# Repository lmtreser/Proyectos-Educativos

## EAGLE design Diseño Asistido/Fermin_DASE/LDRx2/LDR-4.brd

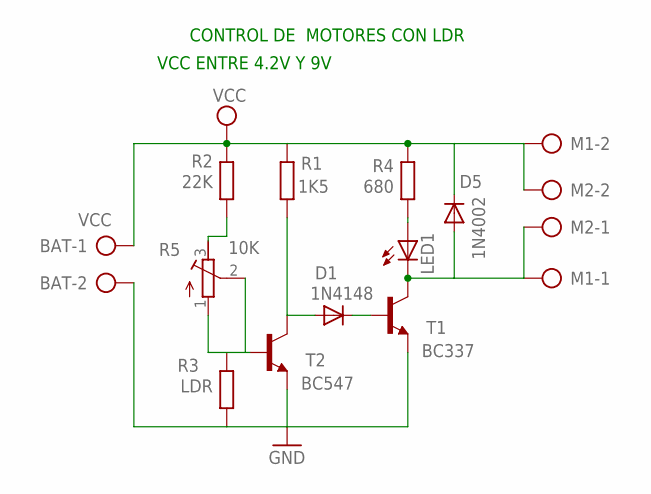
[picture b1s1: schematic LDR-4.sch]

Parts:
BAT: VCC; AK500/2
D1: 1N4148; DO35-7
D5: 1N4002; DO41-10
LED1: LED3MM
M1, M2: AK500/2
R1: 1K5; 0207/7
R2: 22K; 0207/7
R3: LDR; 0204/5
R4: 680; 0207/7
R5: 10K; RTRIM64W
T1: BC337; TO92-CBE
T2: BC547; TO92-CBE

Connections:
GND: BAT.2, R3.1, T1.E, T2.E
unnamed: D1.C, T1.B
unnamed: D1.A, R1.1, T2.C
unnamed: D5.A, LED1.K (C), M1.1, M2.1, T1.C
unnamed: R2.1, R5.3 (E)
unnamed: LED1.A, R4.1
unnamed: R3.2, R5.1 (A), R5.2 (S), T2.B
VCC: BAT.1, D5.C, M1.2, M2.2, R1.2, R2.2, R4.2

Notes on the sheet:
CONTROL DE MOTORES CON LDR
VCC ENTRE 4.2V Y 9V

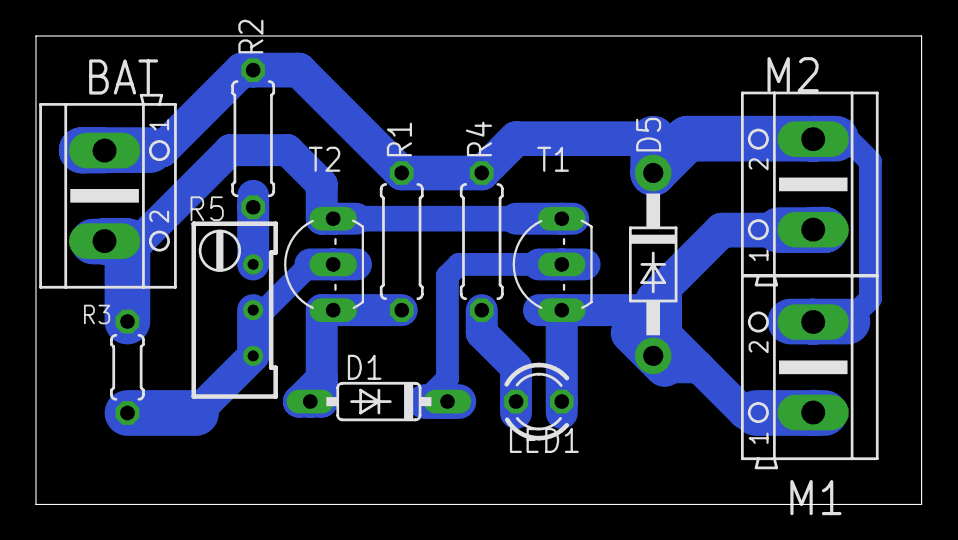
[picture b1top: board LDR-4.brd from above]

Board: 2 copper layers, 49.2 x 26.0 mm, 13 parts (0 on the bottom side), 8 nets.

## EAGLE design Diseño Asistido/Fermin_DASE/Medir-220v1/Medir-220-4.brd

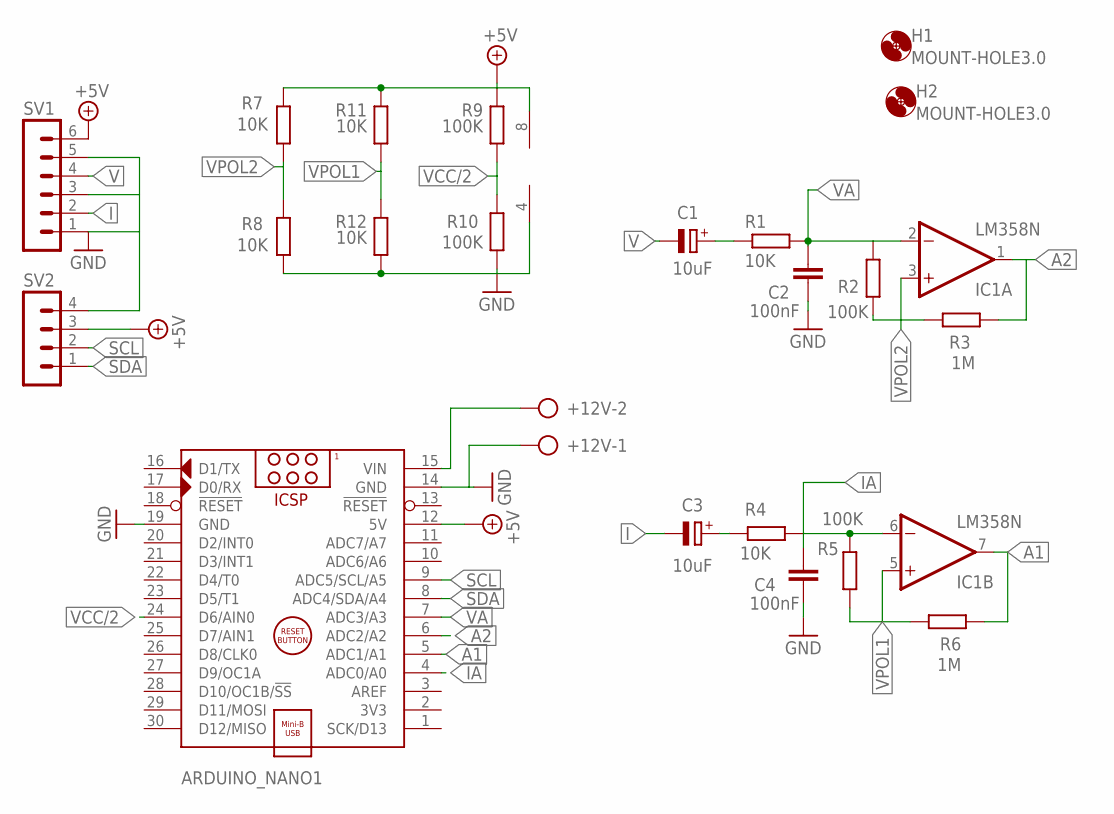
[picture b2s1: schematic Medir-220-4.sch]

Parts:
+12V: AK500/2
ARDUINO_NANO1: ARDUINO_NANO
C1, C3: 10uF; E2,5-5
C2, C4: 100nF; C050-025X075
H1, H2: MOUNT-HOLE3.0; 3,0
IC1: LM358N; DIL08
R1, R4, R7, R8, R11, R12: 10K; 0207/7
R2, R5: 100K; 0207/7
R3, R6: 1M; 0207/7
R9, R10: 100K; 0207/10
SV1: MA06-1
SV2: MA04-1

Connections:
+5V: ARDUINO_NANO1.12 (5V), IC1.8 (V+), R7.1, R9.2, R11.2, SV1.6, SV2.3
A1: ARDUINO_NANO1.5 (ADC1/A1), IC1.7 (OUT), R6.1
A2: ARDUINO_NANO1.6 (ADC2/A2), IC1.1 (OUT), R3.1
GND: +12V.1, ARDUINO_NANO1.14 (GND), ARDUINO_NANO1.19 (GND), C2.2, C4.2, IC1.4 (V-), R8.2, R10.1, R12.1, SV1.1, SV1.3, SV1.5, SV2.4
I: C3.-, SV1.2
IA: ARDUINO_NANO1.4 (ADC0/A0), C4.1, IC1.6 (-IN), R4.1, R5.1
unnamed: C3.+, R4.2
unnamed: C1.+, R1.2
unnamed: +12V.2, ARDUINO_NANO1.15 (VIN)
SCL: ARDUINO_NANO1.9 (ADC5/SCL/A5), SV2.2
SDA: ARDUINO_NANO1.8 (ADC4/SDA/A4), SV2.1
V: C1.-, SV1.4
VA: ARDUINO_NANO1.7 (ADC3/A3), C2.1, IC1.2 (-IN), R1.1, R2.2
VCC/2: ARDUINO_NANO1.24 (D6/AIN0), R9.1, R10.2
VPOL1: IC1.5 (+IN), R5.2, R6.2, R11.1, R12.2
VPOL2: IC1.3 (+IN), R2.1, R3.2, R7.2, R8.1

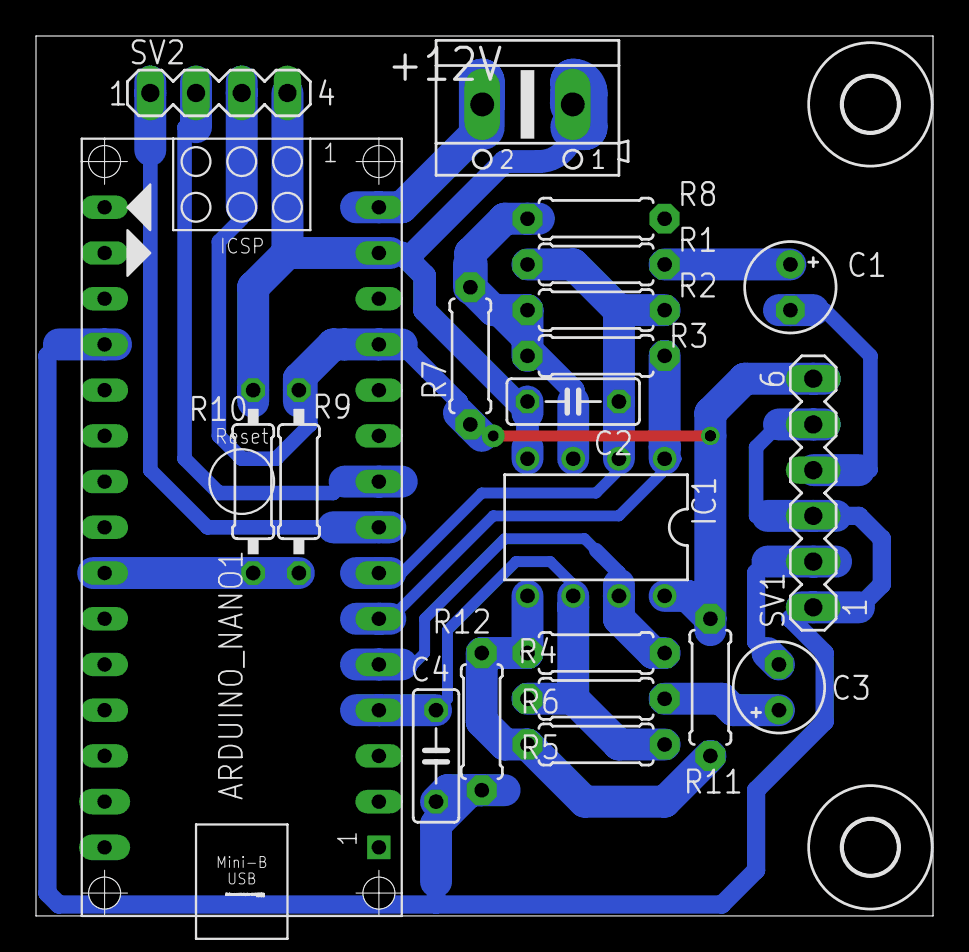
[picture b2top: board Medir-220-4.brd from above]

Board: 2 copper layers, 49.8 x 48.9 mm, 23 parts (0 on the bottom side), 16 nets.

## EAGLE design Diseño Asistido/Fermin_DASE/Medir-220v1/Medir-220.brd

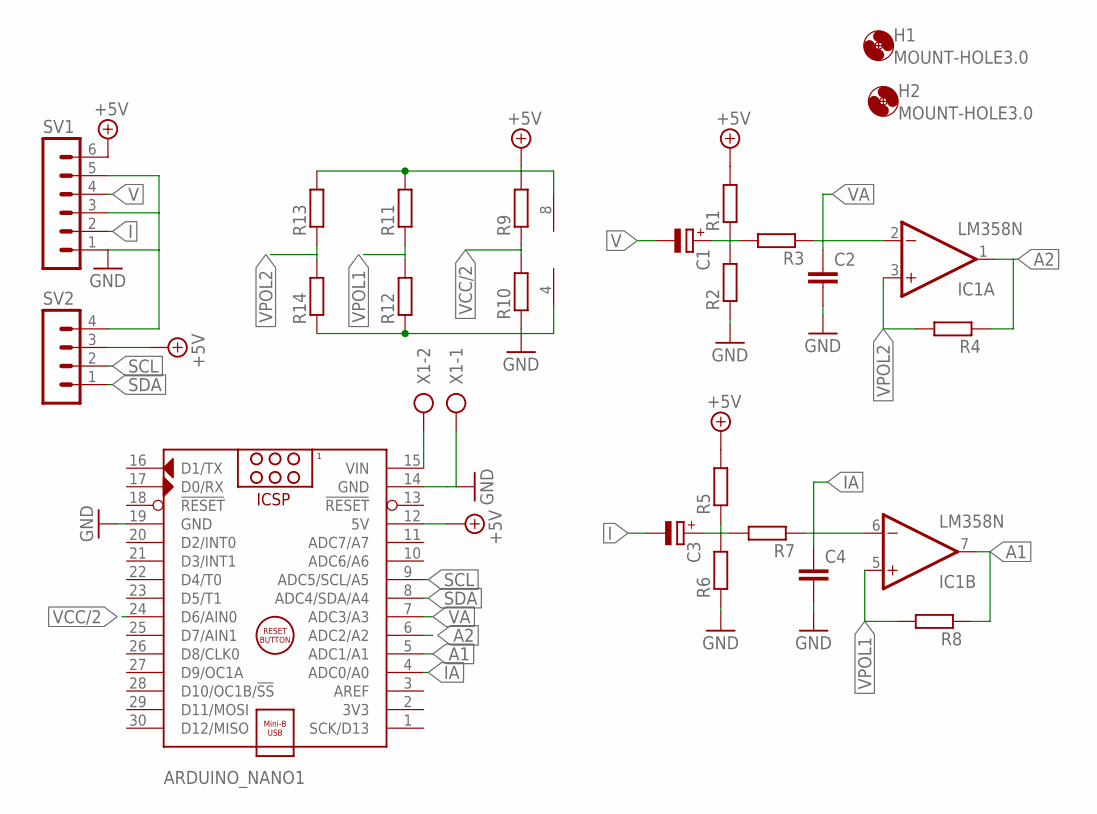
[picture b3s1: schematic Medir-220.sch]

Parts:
ARDUINO_NANO1: ARDUINO_NANO
C1, C3: CPOL-EUE2.5-5; E2,5-5
C2, C4: C-EU050-025X075; C050-025X075
H1, H2: MOUNT-HOLE3.0; 3,0
IC1: LM358N; DIL08
R1, R2, R3, R4, R5, R6, R7, R8, R11, R12, R13, R14: R-EU_0207/7; 0207/7
R9, R10: R-EU_0207/10; 0207/10
SV1: MA06-1
SV2: MA04-1
X1: AK500/2

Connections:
+5V: ARDUINO_NANO1.12 (5V), IC1.8 (V+), R1.2, R5.2, R9.2, R11.2, R13.2, SV1.6, SV2.3
A1: ARDUINO_NANO1.5 (ADC1/A1), IC1.7 (OUT), R8.1
A2: ARDUINO_NANO1.6 (ADC2/A2), IC1.1 (OUT), R4.1
GND: ARDUINO_NANO1.14 (GND), ARDUINO_NANO1.19 (GND), C2.2, C4.2, IC1.4 (V-), R2.1, R6.1, R10.1, R12.1, R14.1, SV1.1, SV1.3, SV1.5, SV2.4, X1.1
I: C3.-, SV1.2
IA: ARDUINO_NANO1.4 (ADC0/A0), C4.1, IC1.6 (-IN), R7.1
unnamed: C1.+, R1.1, R2.2, R3.2
unnamed: C3.+, R5.1, R6.2, R7.2
unnamed: ARDUINO_NANO1.15 (VIN), X1.2
SCL: ARDUINO_NANO1.9 (ADC5/SCL/A5), SV2.2
SDA: ARDUINO_NANO1.8 (ADC4/SDA/A4), SV2.1
V: C1.-, SV1.4
VA: ARDUINO_NANO1.7 (ADC3/A3), C2.1, IC1.2 (-IN), R3.1
VCC/2: ARDUINO_NANO1.24 (D6/AIN0), R9.1, R10.2
VPOL1: IC1.5 (+IN), R8.2, R11.1, R12.2
VPOL2: IC1.3 (+IN), R4.2, R13.1, R14.2

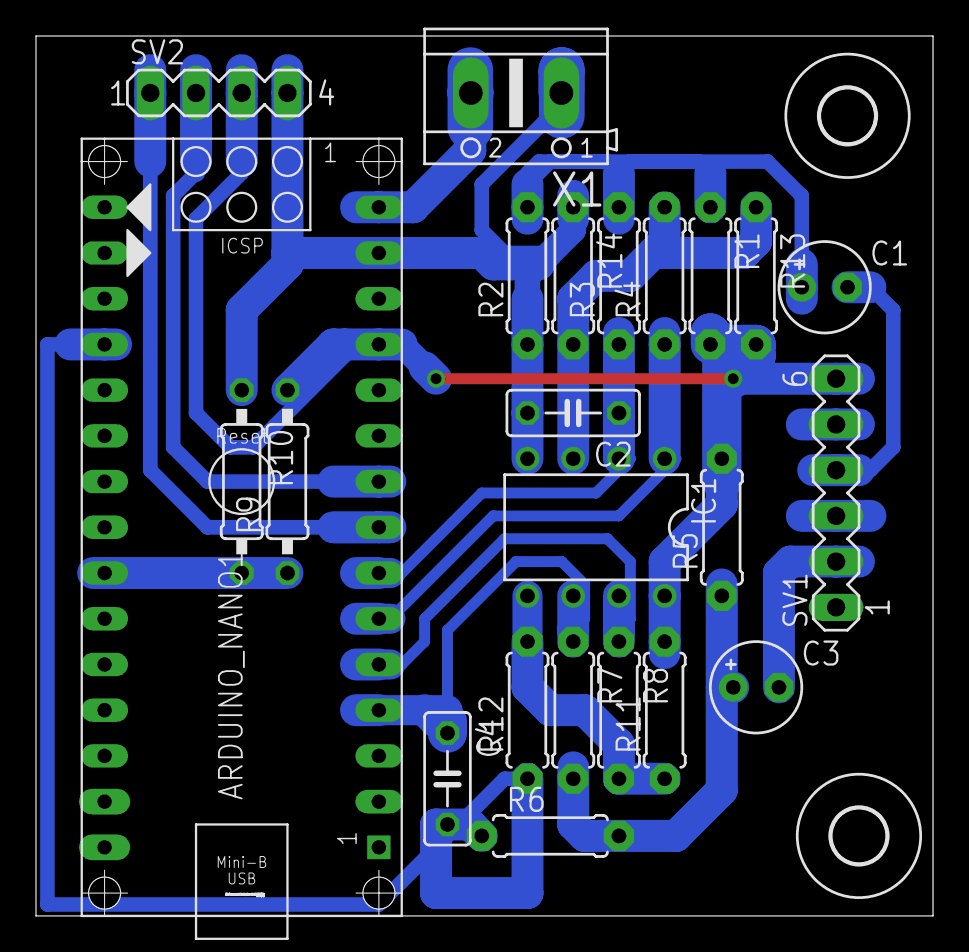
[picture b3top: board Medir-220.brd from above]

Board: 2 copper layers, 49.8 x 48.9 mm, 25 parts (0 on the bottom side), 16 nets.

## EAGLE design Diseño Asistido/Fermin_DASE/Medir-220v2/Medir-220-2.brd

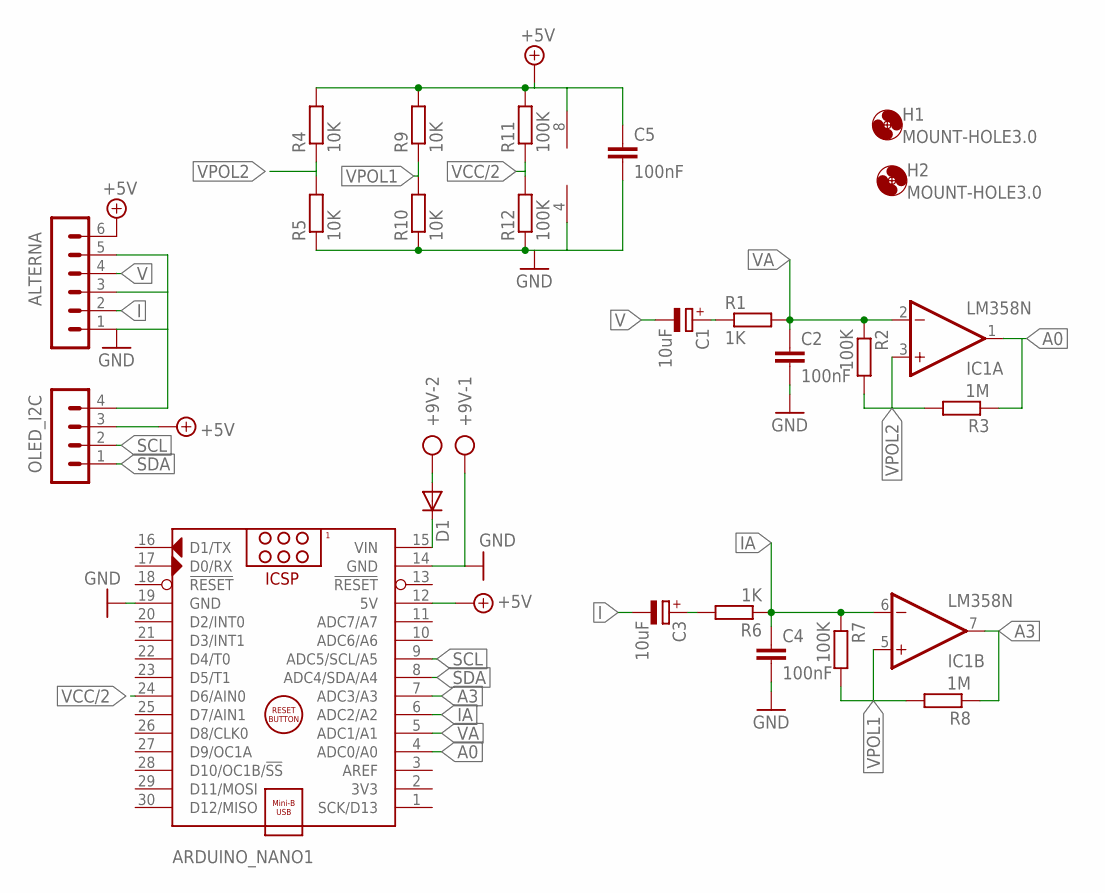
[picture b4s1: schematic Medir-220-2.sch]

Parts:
+9V: AK500/2
ALTERNA: MA06-1
ARDUINO_NANO1: ARDUINO_NANO
C1, C3: 10uF; E2,5-5
C2, C4: 100nF; C050-025X075
C5: 100nF; C025-025X050
D1: DIODE-D-2.5; D-2.5
H1, H2: MOUNT-HOLE3.0; 3,0
IC1: LM358N; DIL08
OLED_I2C: MA04-1
R1, R6: 1K; 0207/7
R2, R7: 100K; 0207/7
R3, R8: 1M; 0207/7
R4: 10K; 0207/10
R5, R9, R10: 10K; 0207/7
R11, R12: 100K; 0207/10

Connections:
+5V: ALTERNA.6, ARDUINO_NANO1.12 (5V), C5.1, IC1.8 (V+), OLED_I2C.3, R4.2, R9.2, R11.2
A0: ARDUINO_NANO1.4 (ADC0/A0), IC1.1 (OUT), R3.1
A3: ARDUINO_NANO1.7 (ADC3/A3), IC1.7 (OUT), R8.1
GND: +9V.1, ALTERNA.1, ALTERNA.3, ALTERNA.5, ARDUINO_NANO1.14 (GND), ARDUINO_NANO1.19 (GND), C2.2, C4.2, C5.2, IC1.4 (V-), OLED_I2C.4, R5.1, R10.1, R12.1
I: ALTERNA.2, C3.-
IA: ARDUINO_NANO1.6 (ADC2/A2), C4.1, IC1.6 (-IN), R6.1, R7.1
unnamed: C1.+, R1.1
unnamed: C3.+, R6.2
unnamed: +9V.2, D1.A
unnamed: ARDUINO_NANO1.15 (VIN), D1.C
SCL: ARDUINO_NANO1.9 (ADC5/SCL/A5), OLED_I2C.2
SDA: ARDUINO_NANO1.8 (ADC4/SDA/A4), OLED_I2C.1
V: ALTERNA.4, C1.-
VA: ARDUINO_NANO1.5 (ADC1/A1), C2.1, IC1.2 (-IN), R1.2, R2.1
VCC/2: ARDUINO_NANO1.24 (D6/AIN0), R11.1, R12.2
VPOL1: IC1.5 (+IN), R7.2, R8.2, R9.1, R10.2
VPOL2: IC1.3 (+IN), R2.2, R3.2, R4.1, R5.2

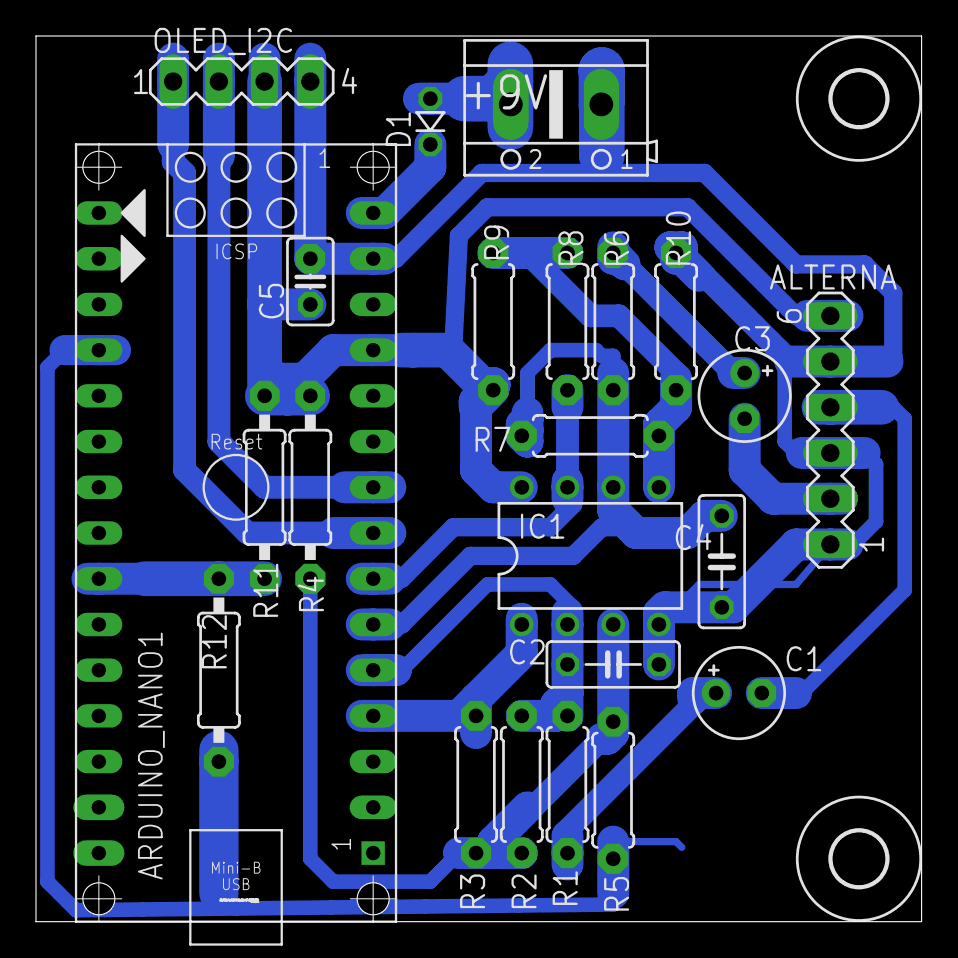
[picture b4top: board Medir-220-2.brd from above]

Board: 2 copper layers, 49.2 x 49.2 mm, 25 parts (0 on the bottom side), 17 nets.

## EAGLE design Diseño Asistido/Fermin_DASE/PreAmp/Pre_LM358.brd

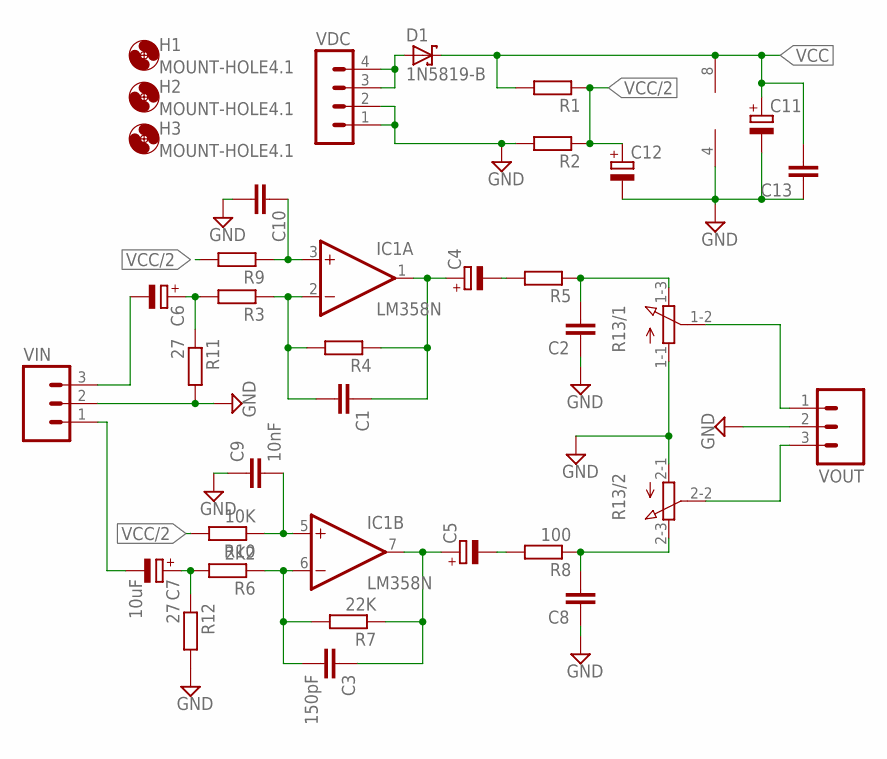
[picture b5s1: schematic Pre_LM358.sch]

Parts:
C1, C2, C8, C10, C13: C-EU025-025X050; C025-025X050
C3: 150pF; C025-025X050
C4, C5, C6: CPOL-EUE2.5-5; E2,5-5
C7: 10uF; E2,5-5
C9: 10nF; C025-025X050
C11: CPOL-EUE2.5-7; E2,5-7
C12: CPOL-EUE2-4; E2-4
D1: 1N5819-B; DO41-7.6
H1, H2, H3: MOUNT-HOLE4.1; 4,1
IC1: LM358N; DIL08
R1, R2, R3, R4, R5, R9: R-EU_0207/7; 0207/7
R6: 2K2; 0207/7
R7: 22K; 0207/7
R8: 100; 0207/7
R10: 10K; 0207/7
R11, R12: 27; 0207/7
R13: 3RP/1610G
VDC: MA04-1
VIN: MA03; 03P
VOUT: MA03; 03P

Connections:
GND: C2.1, C8.1, C9.1, C10.2, C11.-, C12.-, C13.1, IC1.4 (V-), R2.2, R11.2, R12.2, R13.1-1 (A), R13.2-1 (A), VDC.1, VDC.2, VIN.2, VOUT.2
unnamed: C6.+, R3.2, R11.1
unnamed: C7.+, R6.2, R12.1
unnamed: C1.2, IC1.2 (-IN), R3.1, R4.2
unnamed: C1.1, C4.+, IC1.1 (OUT), R4.1
unnamed: C4.-, R5.2
unnamed: C2.2, R5.1, R13.1-3 (E)
unnamed: C3.1, C5.+, IC1.7 (OUT), R7.1
unnamed: C5.-, R8.2
unnamed: C8.2, R8.1, R13.2-3 (E)
unnamed: C3.2, IC1.6 (-IN), R6.1, R7.2
unnamed: C7.-, VIN.1
unnamed: C6.-, VIN.3
unnamed: D1.A, VDC.3, VDC.4
unnamed: R13.2-2 (S), VOUT.3
unnamed: R13.1-2 (S), VOUT.1
unnamed: C10.1, IC1.3 (+IN), R9.1
unnamed: C9.2, IC1.5 (+IN), R10.1
VCC: C11.+, C13.2, D1.C, IC1.8 (V+), R1.2
VCC/2: C12.+, R1.1, R2.1, R9.2, R10.2

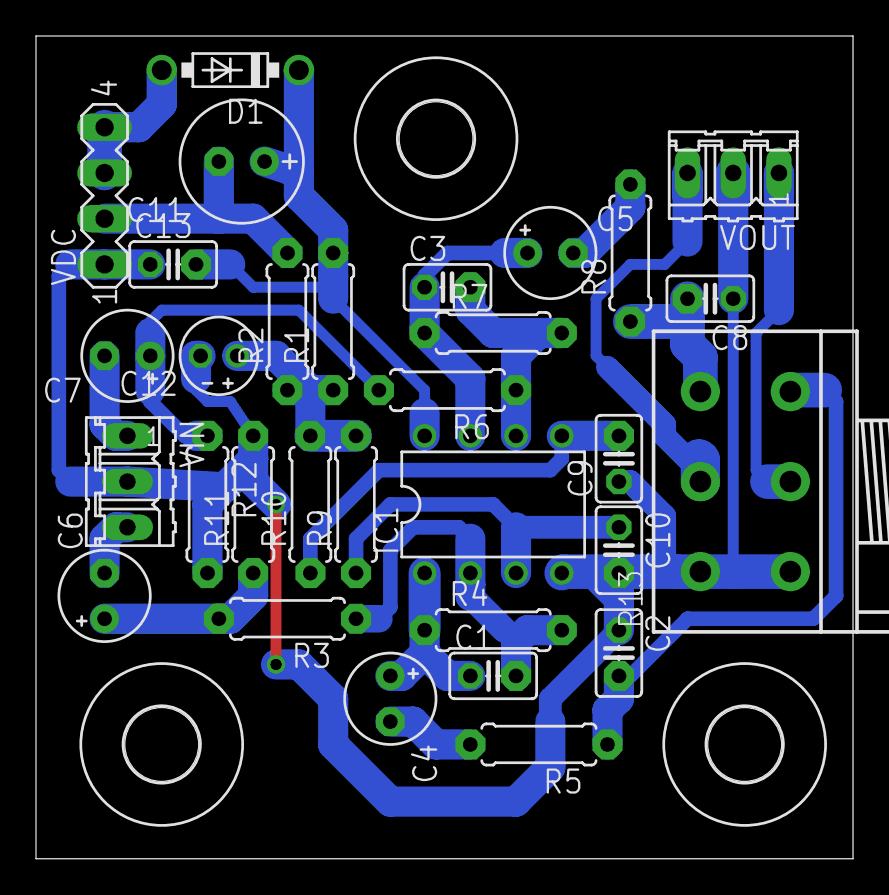
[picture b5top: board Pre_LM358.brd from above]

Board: 2 copper layers, 45.4 x 45.7 mm, 34 parts (0 on the bottom side), 20 nets.

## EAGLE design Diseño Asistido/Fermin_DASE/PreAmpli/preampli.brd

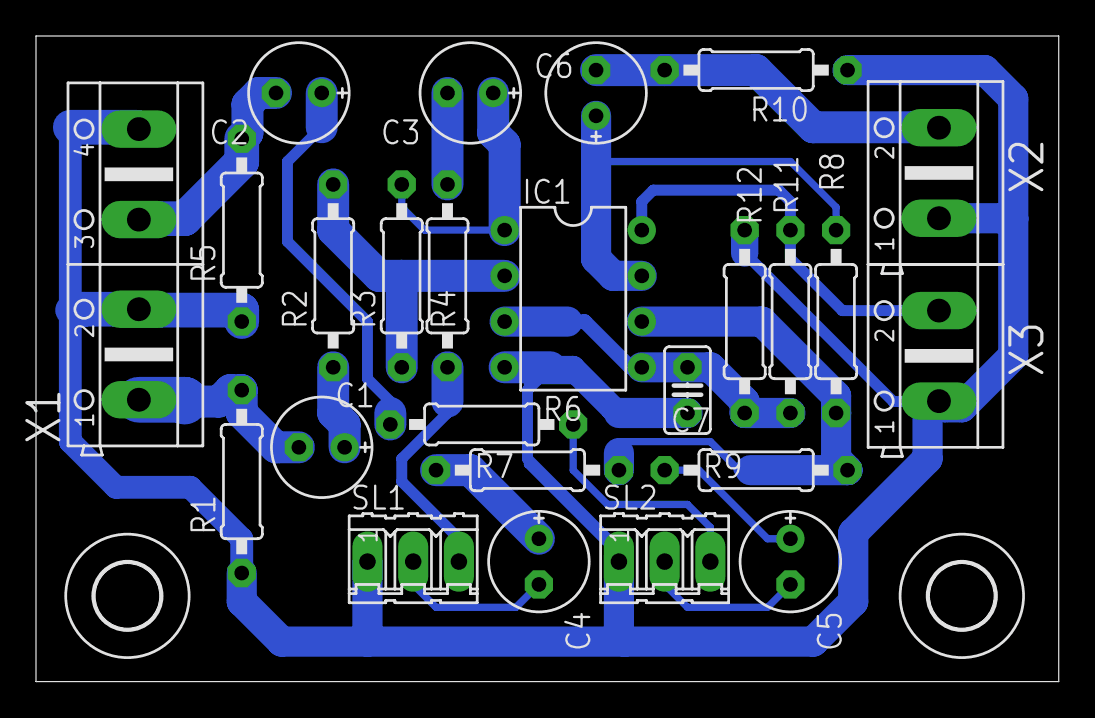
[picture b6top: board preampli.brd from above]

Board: 2 copper layers, 56.8 x 35.9 mm, 27 parts (0 on the bottom side), 19 nets.

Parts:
C1, C2, C3, C4, C5, C6: 10uF; E2,5-6E
C7: 100nF; C025-025X050
E$1, E$2: 3,6
IC1: LM4558N; DIL08
R1, R4, R10: 1K; 0207/10
R2, R5, R7, R9: 10K; 0207/10
R3, R6: 220K; 0207/10
R8: 47K; 0207/10
R11, R12: 100K; 0207/10
SL1: P1; 03P
SL2: P2; 03P
X1: AK500/4
X2, X3: AK500/2

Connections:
GND: C7.2, IC1.4, R1.1, R5.1, R10.1, R12.1, SL1.1, SL2.1, X1.2, X1.4, X2.1, X3.1
unnamed: C2.-, R5.2, X1.3
unnamed: R4.1, SL1.3
unnamed: C1.-, R1.2, X1.1
unnamed: C1.+, R2.1
unnamed: IC1.2, R2.2, R3.1
unnamed: C2.+, R6.1
unnamed: IC1.8, R11.2, X3.2
unnamed: C4.-, SL1.2
unnamed: R6.2, SL2.3
unnamed: C3.-, R4.2
unnamed: C3.+, IC1.1, R3.2
unnamed: C5.-, SL2.2
unnamed: C5.+, R9.1
unnamed: C4.+, R7.1
unnamed: IC1.6, R7.2, R8.1, R9.2
unnamed: C6.-, R10.2, X2.2
unnamed: C6.+, IC1.7, R8.2
VCC2: C7.1, IC1.3, IC1.5, R11.1, R12.2

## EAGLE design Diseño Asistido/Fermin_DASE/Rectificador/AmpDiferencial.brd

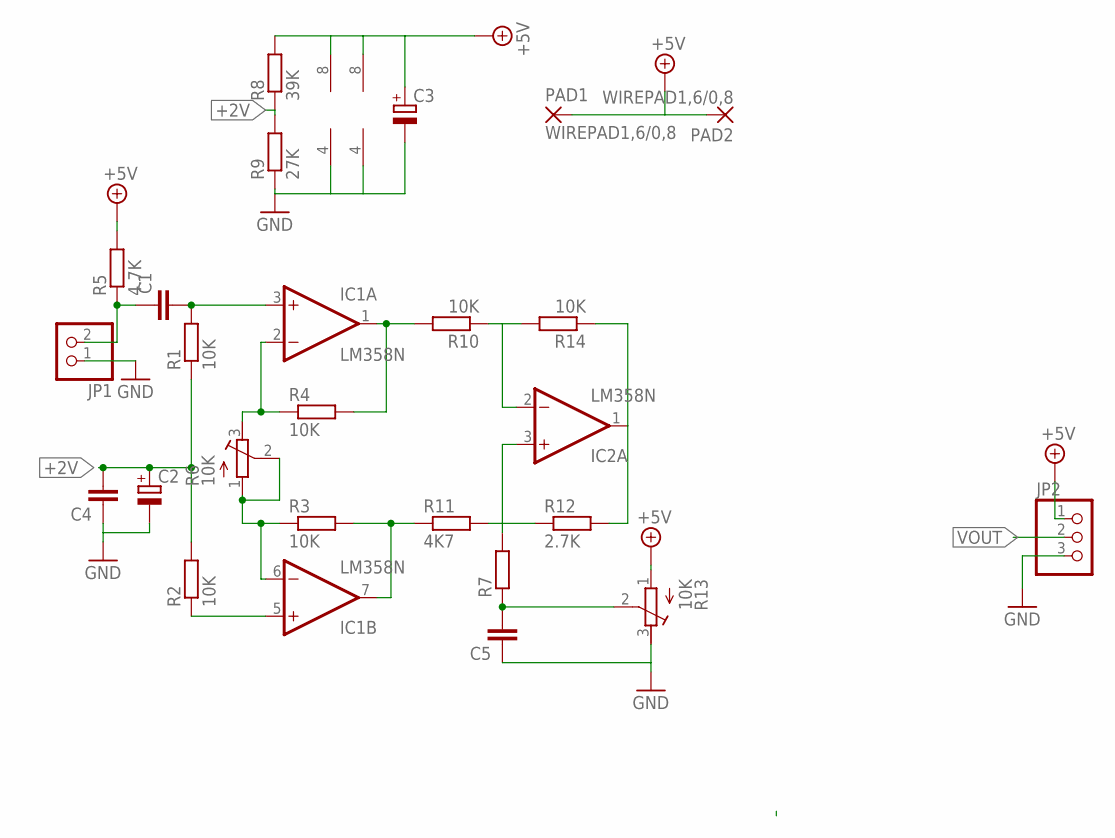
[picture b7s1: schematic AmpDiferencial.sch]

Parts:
C1: C-EU050-025X075; C050-025X075
C2: CPOL-EUE2.5-5; E2,5-5
C3: CPOL-EUE2.5-6; E2,5-6
C4, C5: C-EU025-025X050; C025-025X050
IC1, IC2: LM358N; DIL08
JP1: PINHD-1X2; 1X02
JP2: PINHD-1X3; 1X03
PAD1, PAD2: WIREPAD1,6/0,8; 1,6/0,8
R1, R2, R3, R4, R10, R14: 10K; 0207/7
R5: 4.7K; 0207/7
R6, R13: 10K; RTRIM64W
R7: R-EU_0207/7; 0207/7
R8: 39K; 0207/7
R9: 27K; 0207/7
R11: 4K7; 0207/7
R12: 2.7K; 0207/7

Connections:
+2V: C2.+, C4.2, R1.1, R2.2, R8.1, R9.2
+5V: C3.+, IC1.8 (V+), IC2.8 (V+), JP2.1, PAD1.1, PAD2.1, R5.2, R8.2, R13.1 (A)
GND: C2.-, C3.-, C4.1, C5.1, IC1.4 (V-), IC2.4 (V-), JP1.1, JP2.3, R9.1, R13.3 (E)
unnamed: IC1.2 (-IN), R4.1, R6.3 (E)
unnamed: IC1.1 (OUT), R4.2, R10.2
unnamed: IC1.7 (OUT), R3.2, R11.1
unnamed: C1.1, JP1.2, R5.1
unnamed: IC2.2 (-IN), R10.1, R14.2
unnamed: IC1.6 (-IN), R3.1, R6.1 (A), R6.2 (S)
unnamed: IC1.5 (+IN), R2.1
unnamed: C1.2, IC1.3 (+IN), R1.2
unnamed: IC2.3 (+IN), R7.2, R11.2, R12.1
unnamed: IC2.1 (OUT), R12.2, R14.1
unnamed: C5.2, R7.1, R13.2 (S)
VOUT: JP2.2

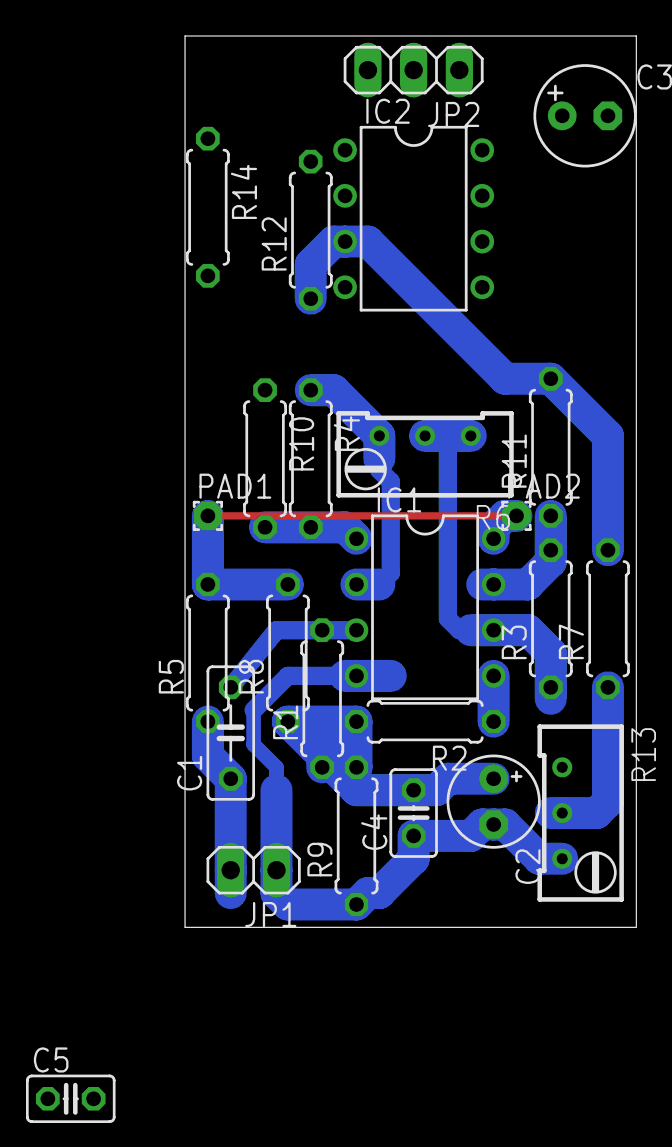
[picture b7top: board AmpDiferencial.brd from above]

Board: 2 copper layers, 25.1 x 49.5 mm, 25 parts (0 on the bottom side), 14 nets.

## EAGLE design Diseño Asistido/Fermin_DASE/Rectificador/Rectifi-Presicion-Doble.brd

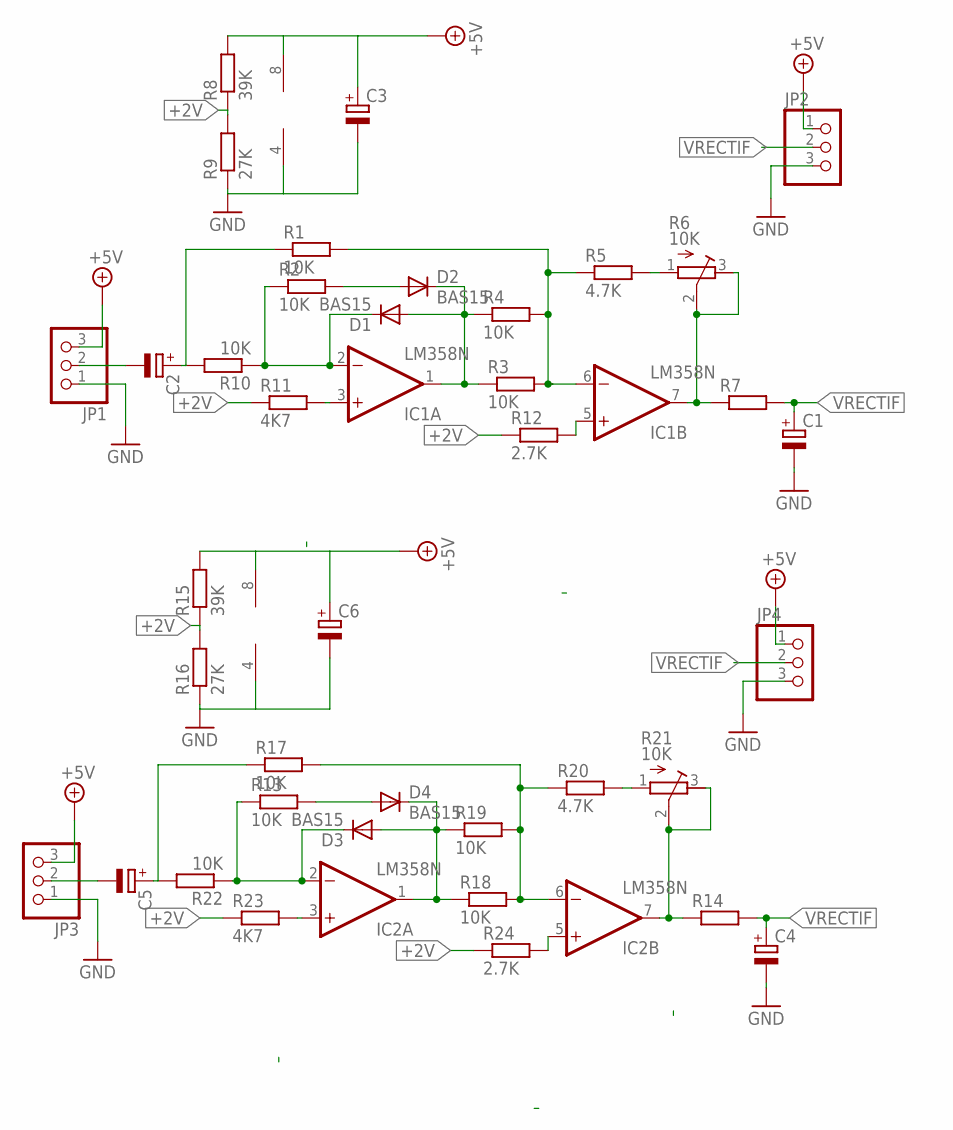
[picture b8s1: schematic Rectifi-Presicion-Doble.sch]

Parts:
C1, C2, C4, C5: CPOL-EUE2.5-5; E2,5-5
C3, C6: CPOL-EUE2.5-6; E2,5-6
D1, D2, D3, D4: BAS15; DO34-7
IC1, IC2: LM358N; DIL08
JP1, JP2, JP3, JP4: PINHD-1X3; 1X03
R1, R2, R3, R4, R10, R13, R17, R18, R19, R22: 10K; 0207/7
R5, R20: 4.7K; 0207/7
R6, R21: 10K; RTRIM64W
R7, R14: R-EU_0207/7; 0207/7
R8, R15: 39K; 0207/7
R9, R16: 27K; 0207/7
R11, R23: 4K7; 0207/7
R12, R24: 2.7K; 0207/7

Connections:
+2V: R8.1, R9.2, R11.1, R12.1, R15.1, R16.2, R23.1, R24.1
+5V: C3.+, C6.+, IC1.8 (V+), IC2.8 (V+), JP1.3, JP2.1, JP3.3, JP4.1, R8.2, R15.2
GND: C1.-, C3.-, C4.-, C6.-, IC1.4 (V-), IC2.4 (V-), JP1.1, JP2.3, JP3.1, JP4.3, R9.1, R16.1
unnamed: D1.A, D2.C, IC1.1 (OUT), R3.1, R4.1
unnamed: C2.+, R1.1, R10.2
unnamed: R5.2, R6.1 (A)
unnamed: D2.A, R2.2
unnamed: D3.A, D4.C, IC2.1 (OUT), R18.1, R19.1
unnamed: IC1.6 (-IN), R1.2, R3.2, R4.2, R5.1
unnamed: D1.C, IC1.2 (-IN), R2.1, R10.1
unnamed: IC1.7 (OUT), R6.2 (S), R6.3 (E), R7.1
unnamed: C2.-, JP1.2
unnamed: IC2.7 (OUT), R14.1, R21.2 (S), R21.3 (E)
unnamed: C5.-, JP3.2
unnamed: IC1.5 (+IN), R12.2
unnamed: R20.2, R21.1 (A)
unnamed: IC2.6 (-IN), R17.2, R18.2, R19.2, R20.1
unnamed: D3.C, IC2.2 (-IN), R13.1, R22.1
unnamed: C5.+, R17.1, R22.2
unnamed: D4.A, R13.2
unnamed: IC2.5 (+IN), R24.2
VPOL: IC1.3 (+IN), R11.2
VPOL1: IC2.3 (+IN), R23.2
VRECTIF: C1.+, C4.+, JP2.2, JP4.2, R7.2, R14.2

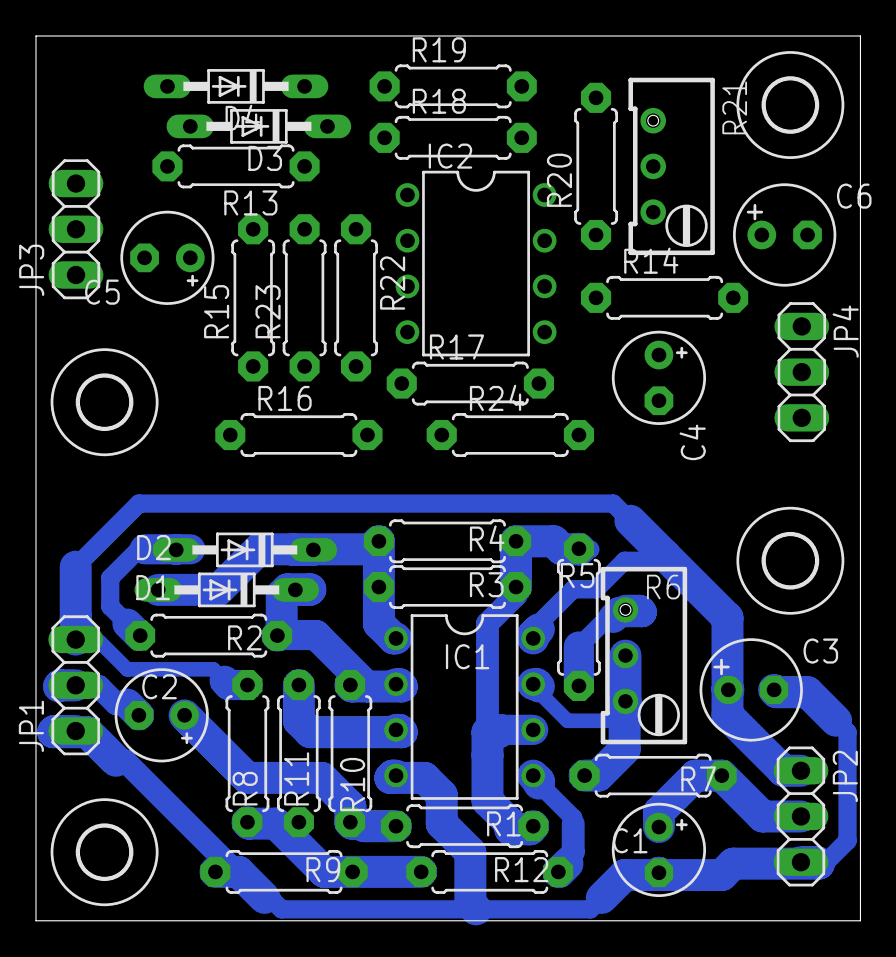
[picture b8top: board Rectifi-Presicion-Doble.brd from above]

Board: 2 copper layers, 45.8 x 49.2 mm, 44 parts (0 on the bottom side), 24 nets.

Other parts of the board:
U$1, U$2, U$3, U$4: 2,8
